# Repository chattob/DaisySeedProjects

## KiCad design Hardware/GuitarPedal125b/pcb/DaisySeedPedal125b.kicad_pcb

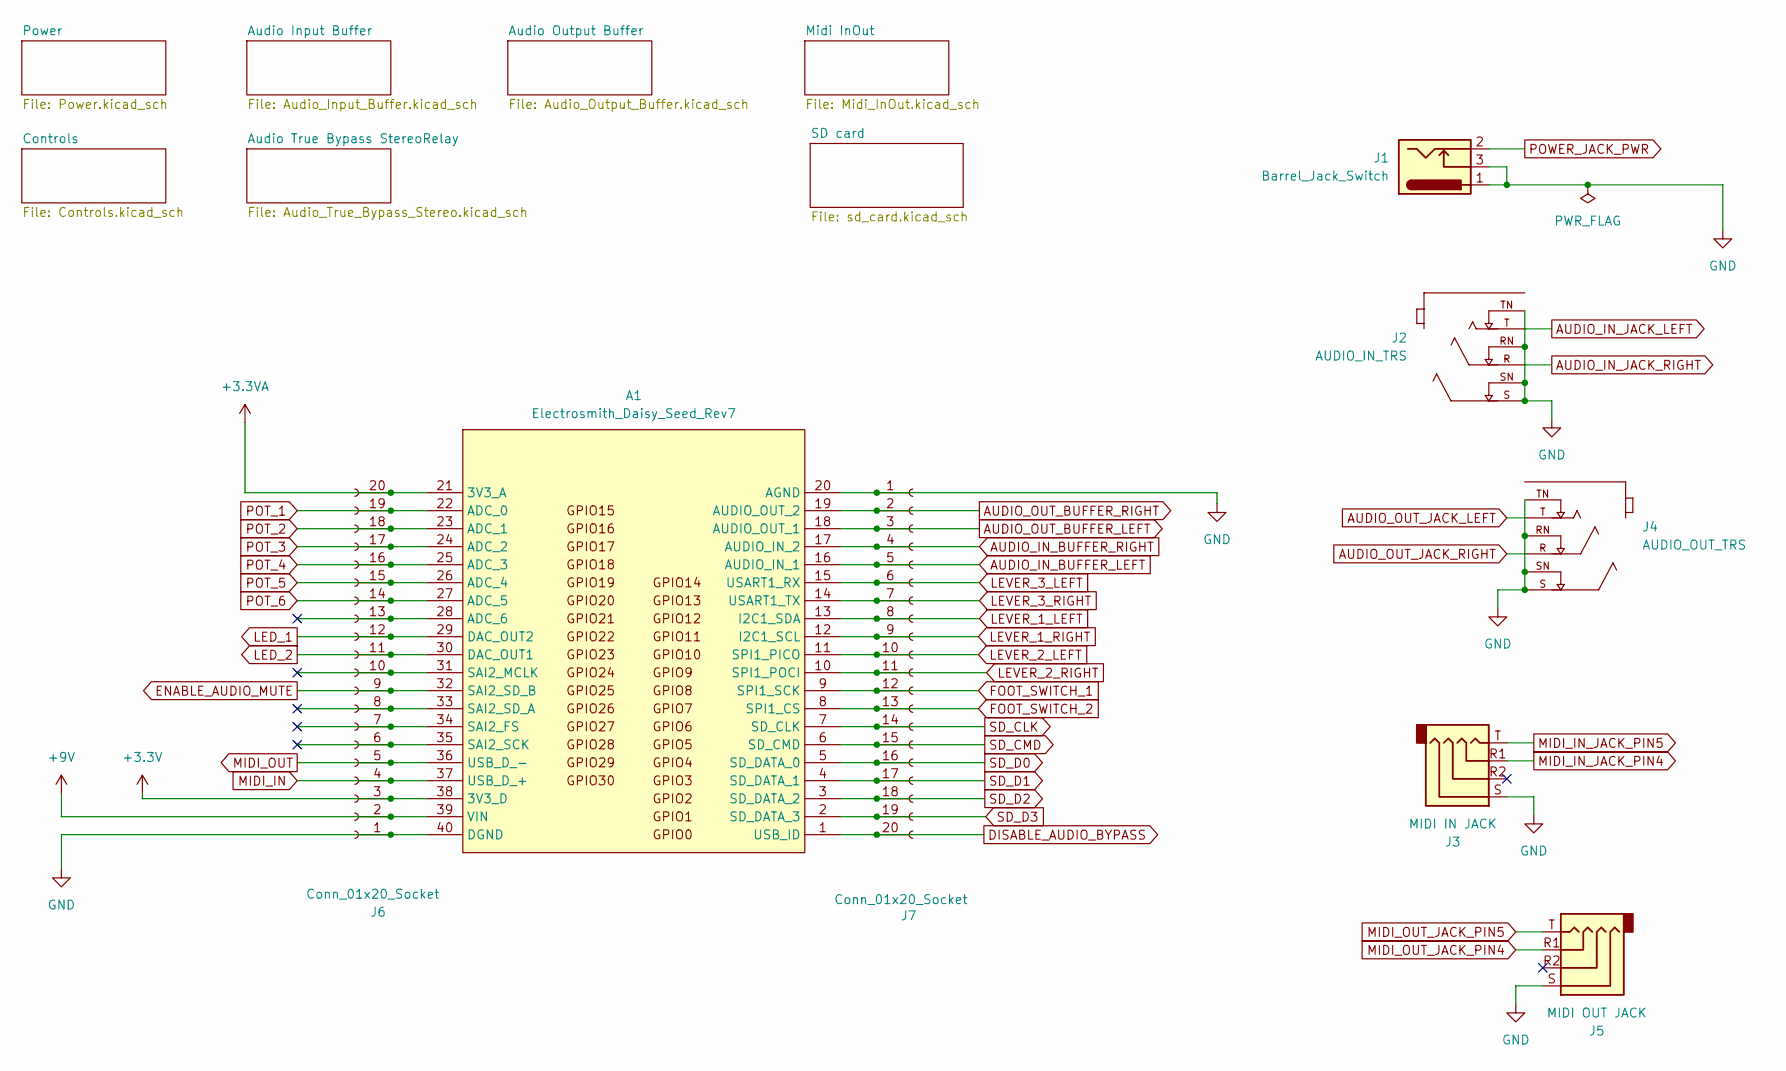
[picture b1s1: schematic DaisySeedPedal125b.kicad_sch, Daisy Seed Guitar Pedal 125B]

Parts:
A1: Electrosmith_Daisy_Seed_Rev7
J1: Barrel_Jack_Switch; Generic_PowerJack; MPN C136744
J2: AUDIO_IN_TRS; Jack_6.35mm_Neutrik_NMJ6HCD2_Horizontal; PARTREV 26.02.2021
J3: MIDI IN JACK; PJ-320A; MPN C2884926
J4: AUDIO_OUT_TRS; Jack_6.35mm_Neutrik_NMJ6HCD2_Horizontal; PARTREV 26.02.2021
J5: MIDI OUT JACK; PJ-320A; MPN C2884926
J6, J7: Conn_01x20_Socket; PinSocket1x20_P2.54mm_Vertical_JLCPCB

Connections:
+3.3V: A1.38 (3V3_D), J6.3; also elsewhere on the board
+3.3VA: A1.21 (3V3_A), J6.20; also elsewhere on the board
+9V: A1.39 (VIN), J6.2; also elsewhere on the board
AUDIO_IN_BUFFER_LEFT: A1.16 (AUDIO_IN_1), J7.5; also elsewhere on the board
AUDIO_IN_BUFFER_RIGHT: A1.17 (AUDIO_IN_2), J7.4; also elsewhere on the board
AUDIO_IN_JACK_LEFT: J2.T; also elsewhere on the board
AUDIO_IN_JACK_RIGHT: J2.R; also elsewhere on the board
AUDIO_OUT_BUFFER_LEFT: A1.18 (AUDIO_OUT_1), J7.3; also elsewhere on the board
AUDIO_OUT_BUFFER_RIGHT: A1.19 (AUDIO_OUT_2), J7.2; also elsewhere on the board
AUDIO_OUT_JACK_LEFT: J4.T; also elsewhere on the board
AUDIO_OUT_JACK_RIGHT: J4.R; also elsewhere on the board
DISABLE_AUDIO_BYPASS: A1.1 (USB_ID), J7.20; also elsewhere on the board
ENABLE_AUDIO_MUTE: A1.32 (SAI2_SD_B), J6.9; also elsewhere on the board
FOOT_SWITCH_1: A1.9 (SPI1_SCK), J7.12; also elsewhere on the board
FOOT_SWITCH_2: A1.8 (SPI1_CS), J7.13; also elsewhere on the board
GND: A1.20 (AGND), A1.40 (DGND), J1.1, J1.3, J2.RN, J2.S, J2.SN, J2.TN, J3.S, J4.RN, J4.S, J4.SN, J4.TN, J5.S, J6.1, J7.1; also elsewhere on the board
LED_1: A1.29 (DAC_OUT2), J6.12; also elsewhere on the board
LED_2: A1.30 (DAC_OUT1), J6.11; also elsewhere on the board
LEVER_1_LEFT: A1.13 (I2C1_SDA), J7.8; also elsewhere on the board
LEVER_1_RIGHT: A1.12 (I2C1_SCL), J7.9; also elsewhere on the board
LEVER_2_LEFT: A1.11 (SPI1_PICO), J7.10; also elsewhere on the board
LEVER_2_RIGHT: A1.10 (SPI1_POCI), J7.11; also elsewhere on the board
LEVER_3_LEFT: A1.15 (USART1_RX), J7.6; also elsewhere on the board
LEVER_3_RIGHT: A1.14 (USART1_TX), J7.7; also elsewhere on the board
MIDI_IN: A1.37 (USB_D_+), J6.4; also elsewhere on the board
MIDI_IN_JACK_PIN4: J3.R1; also elsewhere on the board
MIDI_IN_JACK_PIN5: J3.T; also elsewhere on the board
MIDI_OUT: A1.36 (USB_D_-), J6.5; also elsewhere on the board
MIDI_OUT_JACK_PIN4: J5.R1; also elsewhere on the board
MIDI_OUT_JACK_PIN5: J5.T; also elsewhere on the board
unnamed: A1.28 (ADC_6), J6.13
unnamed: A1.31 (SAI2_MCLK), J6.10
unnamed: A1.33 (SAI2_SD_A), J6.8
unnamed: A1.34 (SAI2_FS), J6.7
unnamed: A1.35 (SAI2_SCK), J6.6
POT_1: A1.22 (ADC_0), J6.19; also elsewhere on the board
POT_2: A1.23 (ADC_1), J6.18; also elsewhere on the board
POT_3: A1.24 (ADC_2), J6.17; also elsewhere on the board
POT_4: A1.25 (ADC_3), J6.16; also elsewhere on the board
POT_5: A1.26 (ADC_4), J6.15; also elsewhere on the board
POT_6: A1.27 (ADC_5), J6.14; also elsewhere on the board
POWER_JACK_PWR: J1.2; also elsewhere on the board
SD_CLK: A1.7 (SD_CLK), J7.14; also elsewhere on the board
SD_CMD: A1.6 (SD_CMD), J7.15; also elsewhere on the board
SD_D0: A1.5 (SD_DATA_0), J7.16; also elsewhere on the board
SD_D1: A1.4 (SD_DATA_1), J7.17; also elsewhere on the board
SD_D2: A1.3 (SD_DATA_2), J7.18; also elsewhere on the board
SD_D3: A1.2 (SD_DATA_3), J7.19; also elsewhere on the board

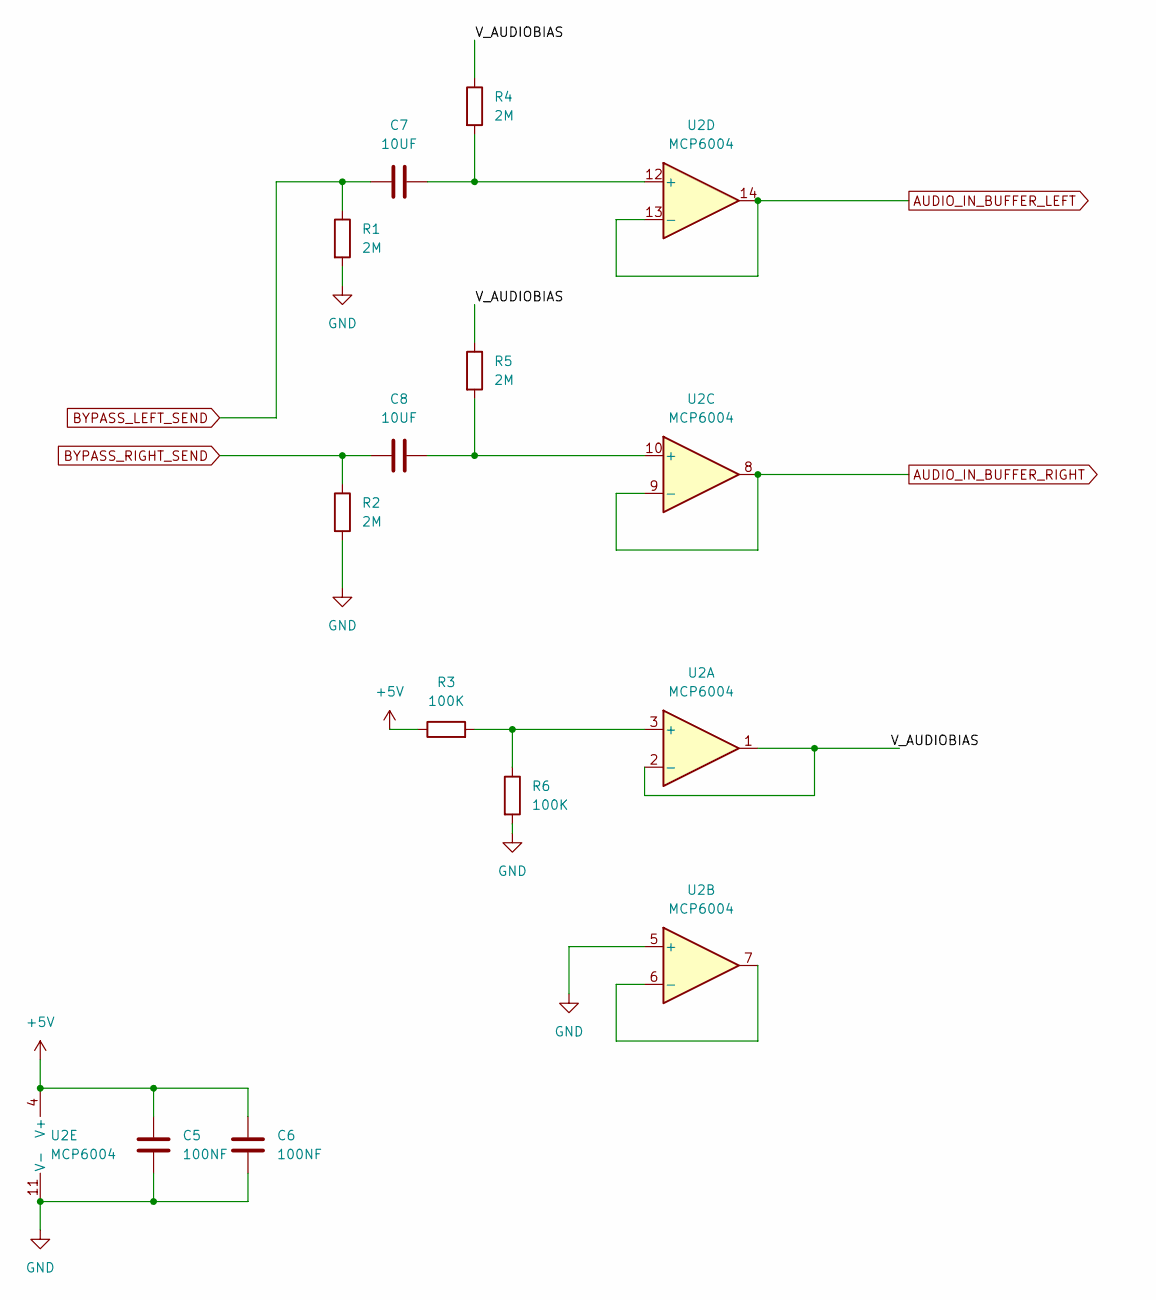
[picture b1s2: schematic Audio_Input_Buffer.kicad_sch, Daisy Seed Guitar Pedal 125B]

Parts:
C5, C6: 100NF; C_0805_2012Metric; MPN C49678
C7, C8: 10UF; C_0805_2012Metric; MPN C15850
R1, R2, R4, R5: 2M; R_0805_2012Metric; MPN C26112
R3, R6: 100K; R_0805_2012Metric; MPN C149504
U2: MCP6004; SOIC-14_3.9x8.7mm_P1.27mm; MPN C7378

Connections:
+5V: C5.1, C6.1, R3.1, U2.4 (V+); also elsewhere on the board
/Audio Input Buffer/V_AUDIOBIAS: R4.1, R5.1, U2.1, U2.2 (-)
AUDIO_IN_BUFFER_LEFT: U2.13 (-), U2.14; also elsewhere on the board
AUDIO_IN_BUFFER_RIGHT: U2.8, U2.9 (-); also elsewhere on the board
BYPASS_LEFT_SEND: C7.1, R1.1; also elsewhere on the board
BYPASS_RIGHT_SEND: C8.1, R2.1; also elsewhere on the board
GND: C5.2, C6.2, R1.2, R2.2, R6.2, U2.5 (+), U2.11 (V-); also elsewhere on the board
unnamed: R3.2, R6.1, U2.3 (+)
unnamed: U2.6 (-), U2.7
unnamed: C8.2, R5.2, U2.10 (+)
unnamed: C7.2, R4.2, U2.12 (+)

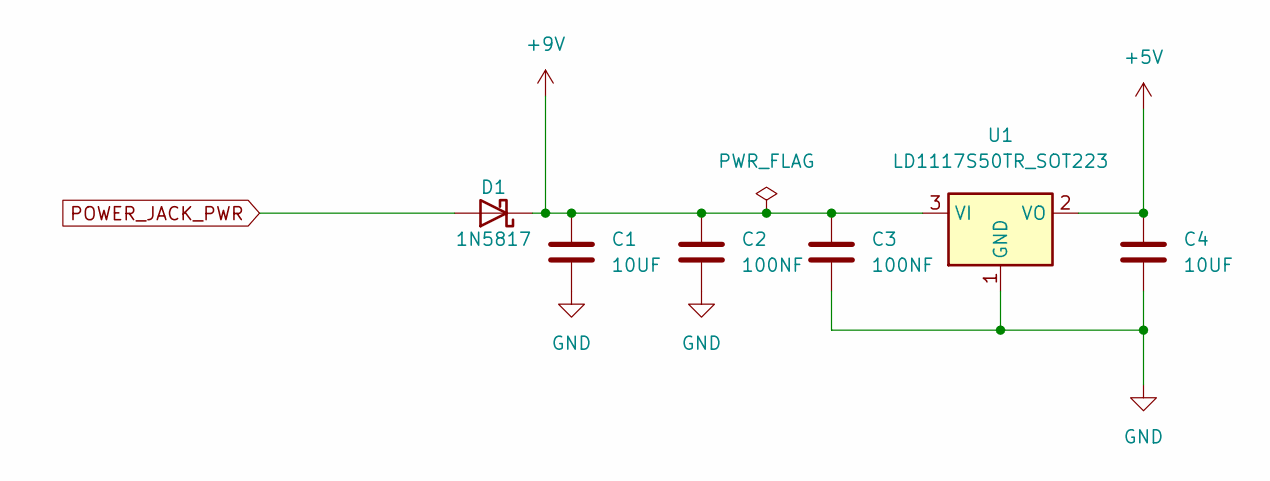
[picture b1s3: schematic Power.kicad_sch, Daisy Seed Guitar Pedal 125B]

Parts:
C1, C4: 10UF; C_0805_2012Metric; MPN C15850
C2, C3: 100NF; C_0805_2012Metric; MPN C49678
D1: 1N5817; D_SOD-123; MPN C727113
U1: LD1117S50TR_SOT223; SOT-223-3_TabPin2; MPN C81157

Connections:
+5V: C4.1, U1.2 (VO); also elsewhere on the board
+9V: C1.1, C2.1, C3.1, D1.1 (K), U1.3 (VI); also elsewhere on the board
GND: C1.2, C2.2, C3.2, C4.2, U1.1 (GND); also elsewhere on the board
POWER_JACK_PWR: D1.2 (A); also elsewhere on the board

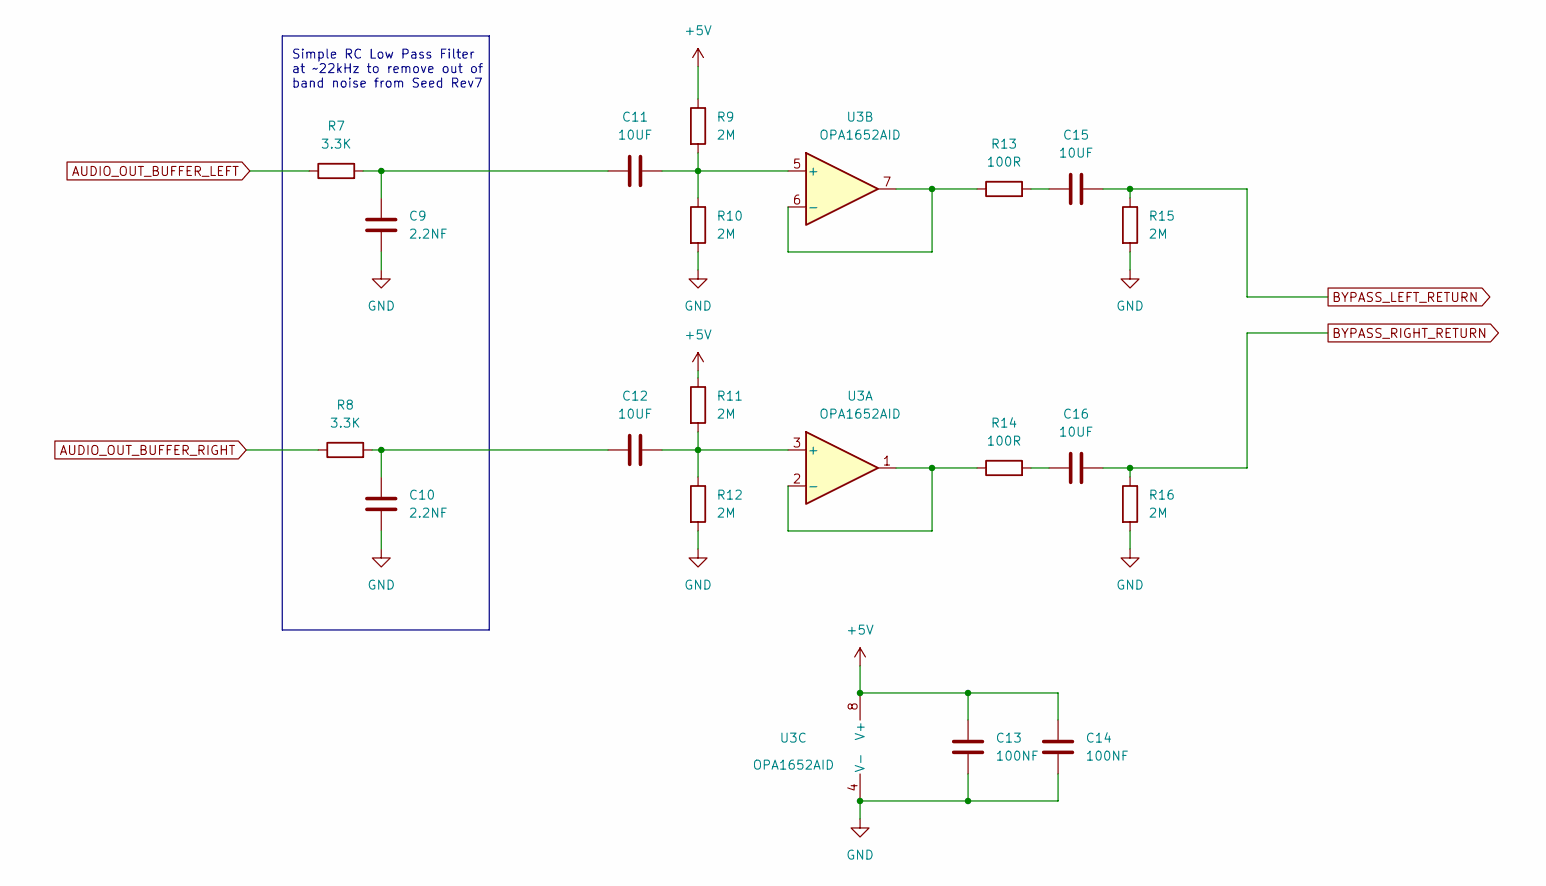
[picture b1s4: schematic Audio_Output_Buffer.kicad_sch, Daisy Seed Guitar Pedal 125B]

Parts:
C9, C10: 2.2NF; C_0805_2012Metric; MPN C28260
C11, C12, C15, C16: 10UF; C_0805_2012Metric; MPN C15850
C13, C14: 100NF; C_0805_2012Metric; MPN C49678
R7, R8: 3.3K; R_0805_2012Metric; MPN C26010
R9, R10, R11, R12, R15, R16: 2M; R_0805_2012Metric; MPN C26112
R13, R14: 100R; R_0805_2012Metric; MPN C17408
U3: OPA1652AID; SOIC-8_3.9x4.9mm_P1.27mm; MPN C30025

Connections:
+5V: C13.1, C14.1, R9.1, R11.1, U3.8 (V+); also elsewhere on the board
AUDIO_OUT_BUFFER_LEFT: R7.1; also elsewhere on the board
AUDIO_OUT_BUFFER_RIGHT: R8.1; also elsewhere on the board
BYPASS_LEFT_RETURN: C15.2, R15.1; also elsewhere on the board
BYPASS_RIGHT_RETURN: C16.2, R16.1; also elsewhere on the board
GND: C9.2, C10.2, C13.2, C14.2, R10.2, R12.2, R15.2, R16.2, U3.4 (V-); also elsewhere on the board
unnamed: C10.1, C12.2, R8.2
unnamed: C9.1, C11.2, R7.2
unnamed: C15.1, R13.2
unnamed: C16.1, R14.2
unnamed: C12.1, R11.2, R12.1, U3.3 (+)
unnamed: R14.1, U3.1, U3.2 (-)
unnamed: C11.1, R9.2, R10.1, U3.5 (+)
unnamed: R13.1, U3.6 (-), U3.7

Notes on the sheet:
Simple RC Low Pass Filter at ~22kHz to remove out of band noise from Seed Rev7

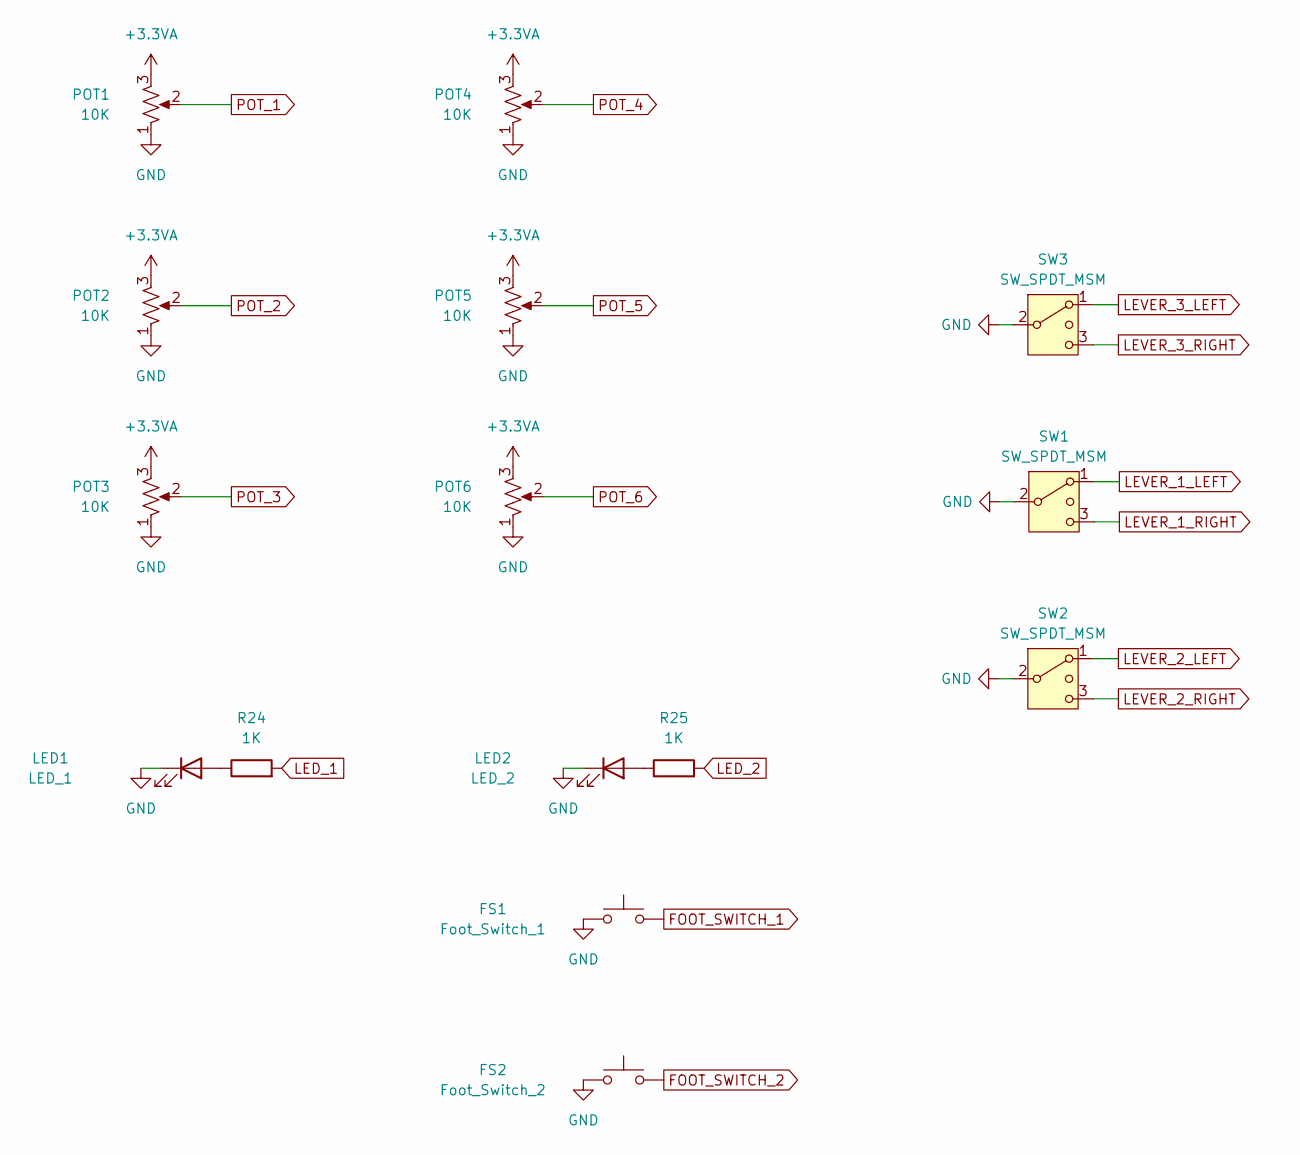
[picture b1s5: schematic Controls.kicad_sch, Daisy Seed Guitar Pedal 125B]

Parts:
FS1: Foot_Switch_1; PinHeader_1x02_P2.54mm_Vertical
FS2: Foot_Switch_2; PinHeader_1x02_P2.54mm_Vertical
LED1: LED_1; PinHeader_1x02_P2.54mm_Vertical
LED2: LED_2; PinHeader_1x02_P2.54mm_Vertical
POT1, POT2, POT3, POT4, POT5, POT6: 10K; Potentiometer_Bourns_PRS11R
R24, R25: 1K; R_0805_2012Metric; MPN C17513
SW1, SW2, SW3: SW_SPDT_MSM; MTS-103

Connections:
+3.3VA: POT1.3, POT2.3, POT3.3, POT4.3, POT5.3, POT6.3; also elsewhere on the board
FOOT_SWITCH_1: FS1.2; also elsewhere on the board
FOOT_SWITCH_2: FS2.2; also elsewhere on the board
GND: FS1.1, FS2.1, LED1.1 (K), LED2.1 (K), POT1.1, POT2.1, POT3.1, POT4.1, POT5.1, POT6.1, SW1.2 (3), SW2.2 (3), SW3.2 (3); also elsewhere on the board
LED_1: R24.2; also elsewhere on the board
LED_2: R25.2; also elsewhere on the board
LEVER_1_LEFT: SW1.1; also elsewhere on the board
LEVER_1_RIGHT: SW1.3 (4); also elsewhere on the board
LEVER_2_LEFT: SW2.1; also elsewhere on the board
LEVER_2_RIGHT: SW2.3 (4); also elsewhere on the board
LEVER_3_LEFT: SW3.1; also elsewhere on the board
LEVER_3_RIGHT: SW3.3 (4); also elsewhere on the board
unnamed: LED1.2 (A), R24.1
unnamed: LED2.2 (A), R25.1
POT_1: POT1.2; also elsewhere on the board
POT_2: POT2.2; also elsewhere on the board
POT_3: POT3.2; also elsewhere on the board
POT_4: POT4.2; also elsewhere on the board
POT_5: POT5.2; also elsewhere on the board
POT_6: POT6.2; also elsewhere on the board

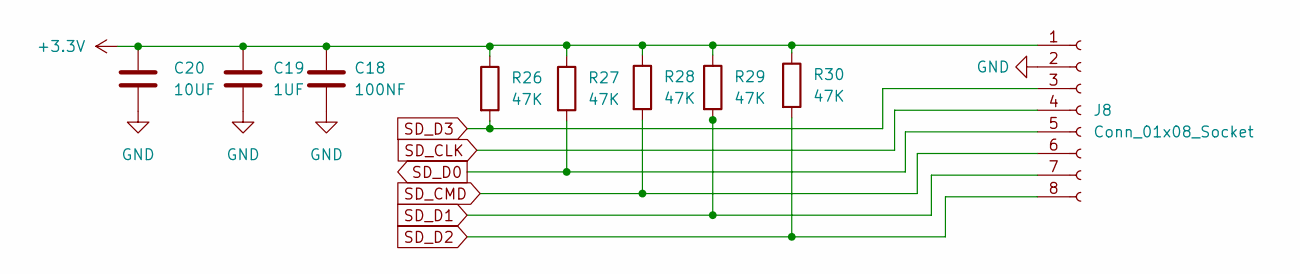
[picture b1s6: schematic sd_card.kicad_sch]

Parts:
C18: 100NF; C_0805_2012Metric
C19: 1UF; C_0805_2012Metric
C20: 10UF; C_0805_2012Metric; MPN C15850
J8: Conn_01x08_Socket; PinHeader_1x08_P2.54mm_Vertical
R26, R27, R28, R29, R30: 47K; R_0805_2012Metric

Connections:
+3.3V: C18.1, C19.1, C20.1, J8.1, R26.1, R27.1, R28.1, R29.1, R30.1; also elsewhere on the board
GND: C18.2, C19.2, C20.2, J8.2; also elsewhere on the board
SD_CLK: J8.4; also elsewhere on the board
SD_CMD: J8.6, R28.2; also elsewhere on the board
SD_D0: J8.5, R27.2; also elsewhere on the board
SD_D1: J8.7, R29.2; also elsewhere on the board
SD_D2: J8.8, R30.2; also elsewhere on the board
SD_D3: J8.3, R26.2; also elsewhere on the board

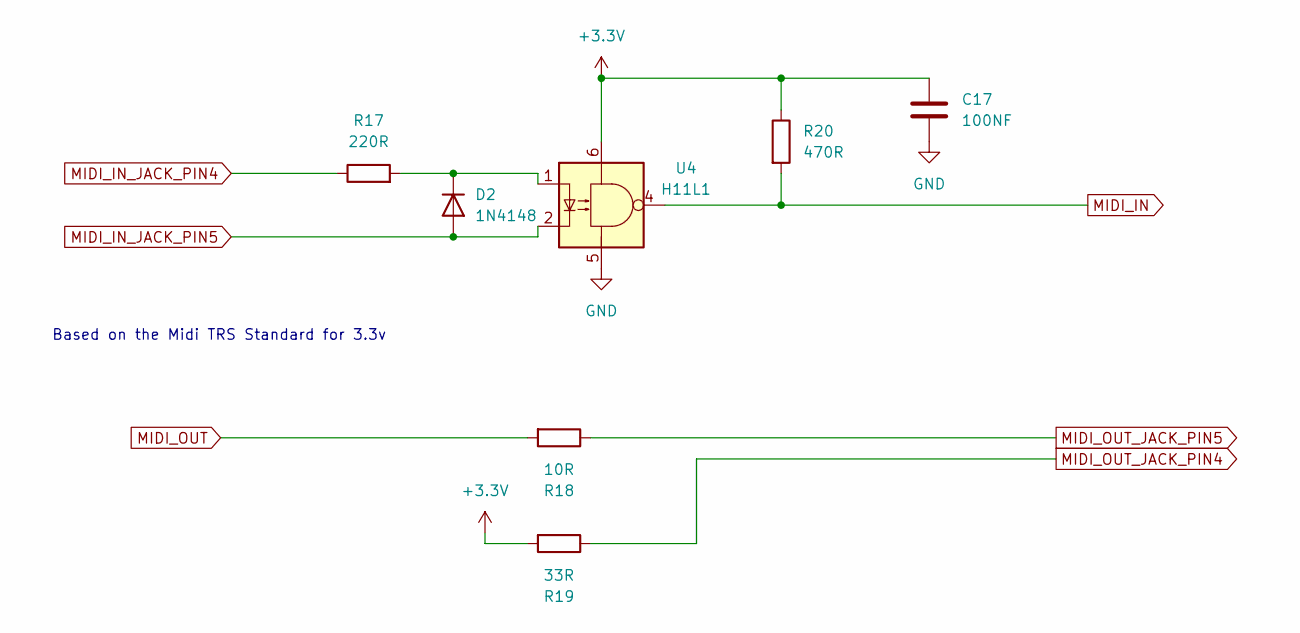
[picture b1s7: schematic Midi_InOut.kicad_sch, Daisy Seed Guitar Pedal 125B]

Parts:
C17: 100NF; C_0805_2012Metric; MPN C49678
D2: 1N4148; D_SOD-123; MPN C81598
R17: 220R; R_0805_2012Metric; MPN C17557
R18: 10R; R_0805_2012Metric; MPN C17415
R19: 33R; R_0805_2012Metric; MPN C17634
R20: 470R; R_0805_2012Metric; MPN C17710
U4: H11L1; SOP-6_2.54mm; MPN C78589

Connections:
+3.3V: C17.1, R19.2, R20.1, U4.6; also elsewhere on the board
GND: C17.2, U4.5; also elsewhere on the board
MIDI_IN: R20.2, U4.4; also elsewhere on the board
MIDI_IN_JACK_PIN4: R17.1; also elsewhere on the board
MIDI_IN_JACK_PIN5: D2.2 (A), U4.2; also elsewhere on the board
MIDI_OUT: R18.2; also elsewhere on the board
MIDI_OUT_JACK_PIN4: R19.1; also elsewhere on the board
MIDI_OUT_JACK_PIN5: R18.1; also elsewhere on the board
unnamed: D2.1 (K), R17.2, U4.1

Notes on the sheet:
Based on the Midi TRS Standard for 3.3v

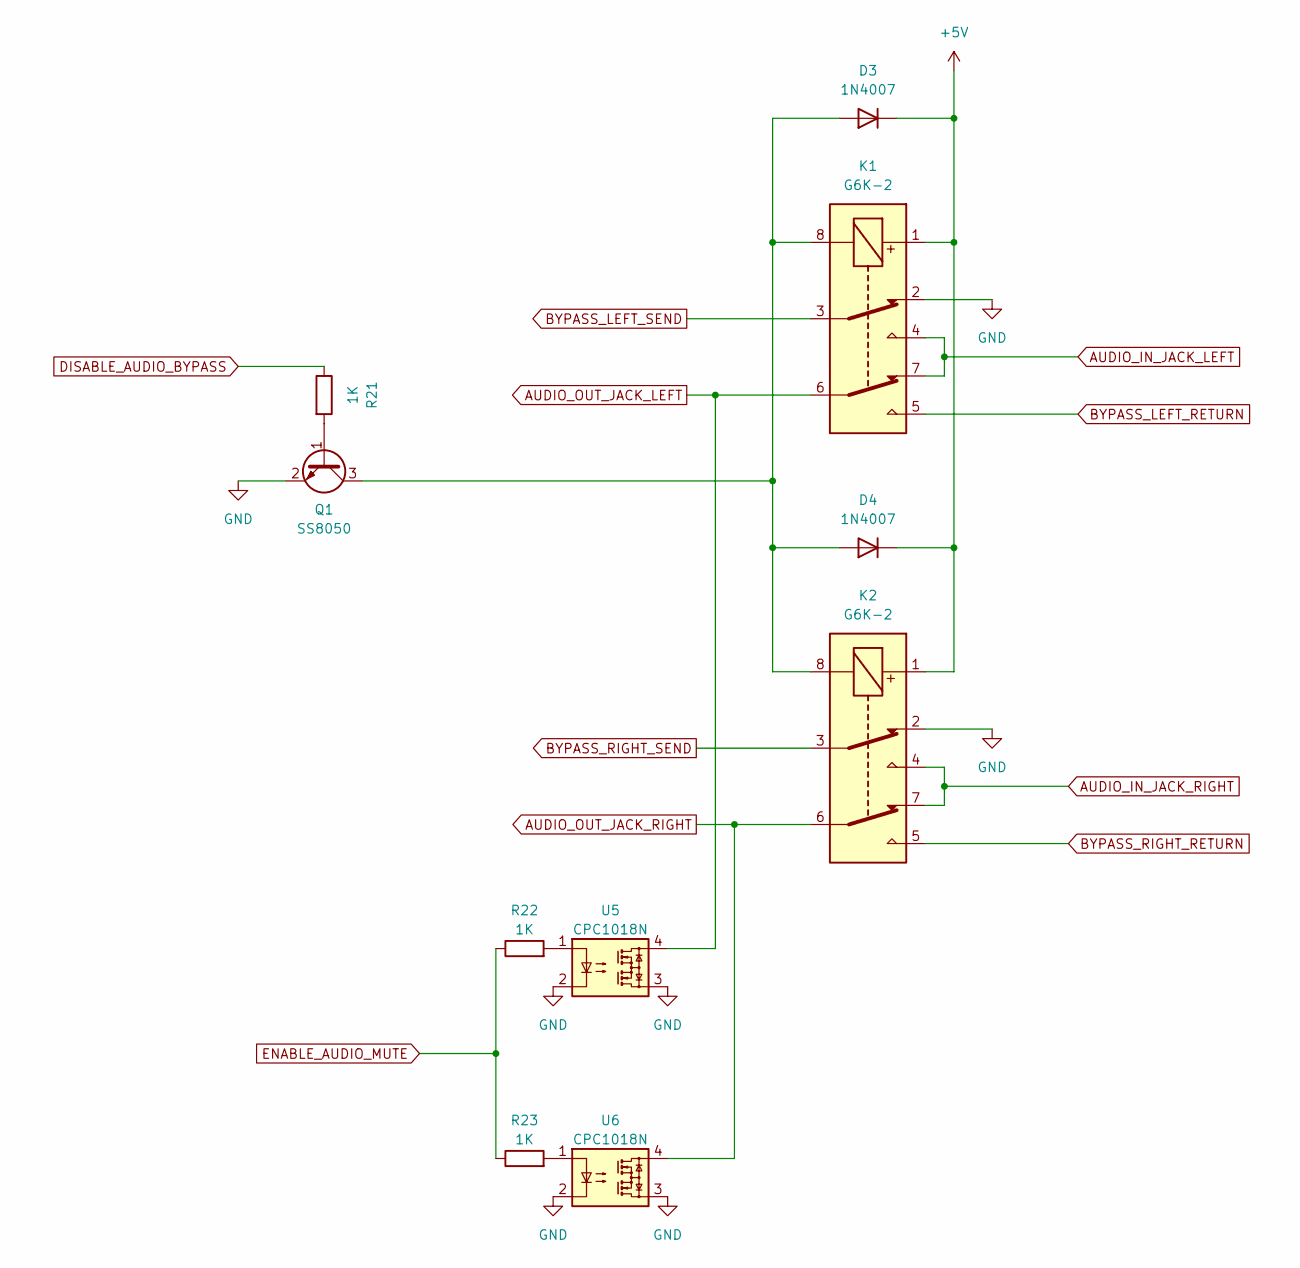
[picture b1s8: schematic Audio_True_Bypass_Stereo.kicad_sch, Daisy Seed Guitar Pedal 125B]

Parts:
D3, D4: 1N4007; D_SOD-123F; MPN C108803
K1, K2: G6K-2; Relay_DPDT_Omron_G6K-2G-Y; MPN C397140
Q1: SS8050; SOT-23-3; MPN C2150
R21, R22, R23: 1K; R_0805_2012Metric; MPN C17513
U5, U6: CPC1018N; SOP-4_3.8x4.1mm_P2.54mm; MPN C133069

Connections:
+5V: D3.1 (K), D4.1 (K), K1.1, K2.1; also elsewhere on the board
AUDIO_IN_JACK_LEFT: K1.4, K1.7; also elsewhere on the board
AUDIO_IN_JACK_RIGHT: K2.4, K2.7; also elsewhere on the board
AUDIO_OUT_JACK_LEFT: K1.6, U5.4; also elsewhere on the board
AUDIO_OUT_JACK_RIGHT: K2.6, U6.4; also elsewhere on the board
BYPASS_LEFT_RETURN: K1.5; also elsewhere on the board
BYPASS_LEFT_SEND: K1.3; also elsewhere on the board
BYPASS_RIGHT_RETURN: K2.5; also elsewhere on the board
BYPASS_RIGHT_SEND: K2.3; also elsewhere on the board
DISABLE_AUDIO_BYPASS: R21.1; also elsewhere on the board
ENABLE_AUDIO_MUTE: R22.1, R23.1; also elsewhere on the board
GND: K1.2, K2.2, Q1.2 (E), U5.2, U5.3, U6.2, U6.3; also elsewhere on the board
unnamed: D3.2 (A), D4.2 (A), K1.8, K2.8, Q1.3 (C)
unnamed: Q1.1 (B), R21.2
unnamed: R22.2, U5.1
unnamed: R23.2, U6.1

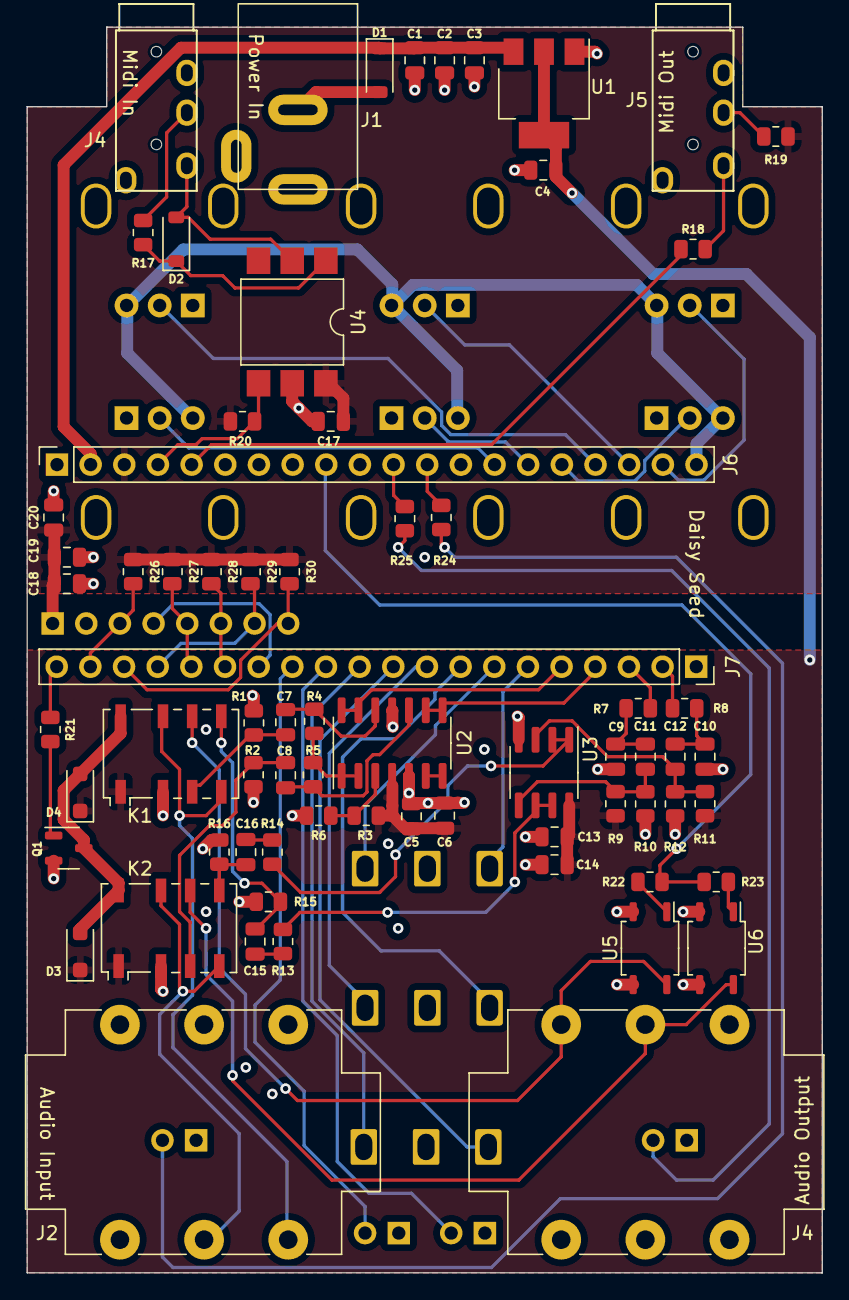
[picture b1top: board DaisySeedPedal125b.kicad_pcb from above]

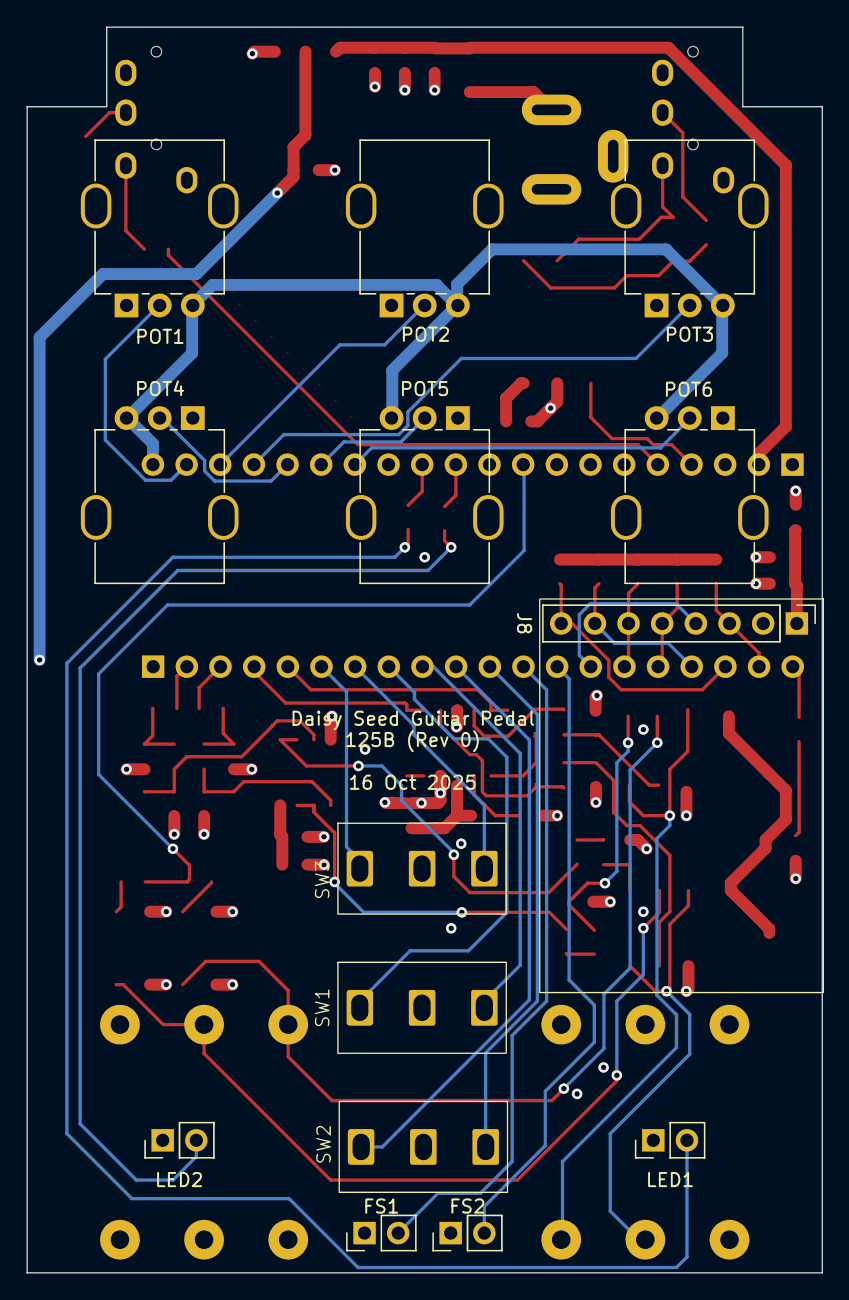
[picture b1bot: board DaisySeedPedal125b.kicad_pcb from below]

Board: 4 copper layers, 60.0 x 94.0 mm, 84 parts (14 on the bottom side), 68 nets.

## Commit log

2025-11-23 Replace screen and encoder by 3 toggle switches and SD card reader.
2025-11-23 Refactor for effect chain. Remove undesired effects.
2025-11-23 Remove phase vocoder: to be developped in separate branch.
2025-11-23 Modify .vscode
2025-11-24 Activate modifiers with alt switch.
2025-11-27 Add pitch shifter.
2025-11-27 Wraparound blink, layer change blink.
2025-11-28 Optimize cpu usage.
2025-11-29 Enabling/disabling pitch shifter with switch.
2025-11-29 Writing functionnal.
2025-12-03 Saving with layer name.
2025-12-09 fixed wavwriter. new distortion. new filter. lambda knob mapping. airwindows mackity (unused).
2025-12-10 Distortion: volume normalization.
2025-12-10 Read midi clock.
2025-12-11 Sync looper.
2025-12-11 Fix knob routes.
2025-12-23 Fix openocd path
2026-01-06 Fix bound checks in base effect module.
2026-01-06 Use structured globals.
2026-01-07 Clamp selection to existing layers and absolute max
2026-01-10 Replace pitch shifter with bandshifting octave generator
2026-01-11 Add it
2026-01-14 Initial micro-looper
2026-01-14 Stretching the loop.
2026-01-18 Dual playhead.
2026-01-19 Sampler mode
2026-01-27 Fixes.
2026-01-27 Early stretched playback.
2026-01-27 Add polyoctave.
2026-01-27 Enveloppe autostart.
2026-01-27 Add distortion and delay.
2026-01-27 Bitcrusher.
2026-01-28 Double buffering.
2026-01-28 Input mixing.
2026-01-28 Ping pong reading of stretched loop.
2026-01-29 Behaviour not too bad
2026-01-30 Smoothed speed error.
2026-01-31 Markov chain speed error.
2026-01-31 Playing head pingpong.
2026-02-01 Crop stretched playback range to avoid boundaries volume dips.
2026-02-01 Attack parameter.
2026-02-02 Randomized SSR.
2026-02-04 Selectable reverb mode.
2026-02-04 fixing looper mode: wip
2026-02-06 Reduce stretch factor.
2026-02-06 Stretch harmony head.
2026-02-19 Preparing for stereo + double-tap switch
2026-02-20 Working on footswitch behaviour
2026-02-22 Pre-looper delay
2026-02-22 Separate tape module.
2026-02-23 MIDI routing.
2026-02-24 Multi-layer looper instead of pre-delay
2026-03-03 Fighting stretch computing noise
2026-03-04 launch json modification
2026-03-04 User manual
2026-03-12 Update libDaisy submodule for BOOT_SRAM .sram_bss fix
2026-03-19 Change FFT size to 8192
2026-03-21 Move back to per sample processing (prepare reverb split)
2026-03-22 Randomize ping-pong bounce
